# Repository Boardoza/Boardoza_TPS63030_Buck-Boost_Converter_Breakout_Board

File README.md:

# Boardoza TPS63030 Buck-Boost Converter Breakout Board
The TPS63030 High-Efficiency Buck-Boost Converter Breakout Board is a versatile power solution designed for battery-operated devices. It leverages the TPS63030 IC to efficiently convert input voltages from a wide range of battery chemistries, including two-cell or three-cell alkaline, NiCd, NiMH, or single-cell Li-ion/Li-polymer batteries. This board ensures a stable and adjustable power supply, supporting output currents up to 600 mA, even when the battery discharges to as low as 2.5V. With its high efficiency, compact design, and low quiescent current, the TPS63030 breakout board is ideal for portable electronics, wearable devices, and other applications requiring consistent performance regardless of battery charge state.

### [Click here to purchase!](https://www.ozdisan.com/maker-and-iot-products/boardoza/boardoza-modules/BOARDOZA-TPS63030/1206513)

|Front Side|Back Side|
|:---:|:---:|
| | |

---
## Key Features
- High Efficiency: Provides efficient power conversion, achieving up to 96% efficiency for extended battery life.
- Buck-Boost Capability: Supports both step-up and step-down voltage conversion for versatile power management.
- Adjustable Output Voltage: Allows for precise voltage control to match various device requirements.
- Automatic Mode Transition: Seamlessly transitions between step-down and boost modes based on input voltage.
- Safety Features: Includes overtemperature protection and load disconnect during shutdown for enhanced device safety.
- Compact Design: Small form factor for easy integration into portable applications and battery-operated devices.
- Low Quiescent Current: Consumes less than 50 μA in standby mode, optimizing power efficiency.

---

## Technical Specifications
**Input Voltage:**	1.8V ~ 5.5V

**Power Input Type:** Molex 2 pin 2.50 header

**Output Voltage:** 3.3V	

**Output Current:** 
- Up to 800 mA in Step-Down Mode (VIN = 3.6V to 5.5V)  
- Up to 500 mA in Boost Mode (VIN > 2.4V)  
 
**Functions:**	Buck-Boost Converter

**Efficiency:** Up to 96%

**Quiescent Current:** Less than 50 μA  

**Operating Temperature:**	-40°C ~ +85°C

**Board Dimensions:**	40mm x 60mm

---

## Board Pinout
| ( J1 ) Pin Number | Pin Name | Description |
|:---:|:---:|---|
| 1 | GND | Ground |
| 2 | VIN | Voltage Input Pin (1.8V ~ 5.5V) |

| ( J2 ) Pin Number | Pin Name | Description |
|:---:|:---:|---|
| 1 | GND | Ground |
| 2 | VIN SENSE | Can be used to measure the input voltage directly on the input capacitor. |

| ( J3 ) Pin Number | Pin Name | Description |
|:---:|:---:|---|
| 1 | HIGH | Power Supply |
| 2 | EN | Shorting jumper between the center pin EN and HIGH turns on the unit. Shorting jumper between the center pin EN and LOW turns the unit off. (Default: Pulled up to VIN in circuit) |
| 3 | LOW | Ground |

| ( J4 ) Pin Number | Pin Name | Description |
|:---:|:---:|---|
| 1 | GND | Ground |
| 2 | VOUT SENSE | Can be used to measure the output voltage directly on the output capacitor. |

| ( J5 ) Pin Number | Pin Name | Description |
|:---:|:---:|---|
| 1 | HIGH | Power Supply |
| 2 | PS/SYNC | The center pin of this jumpers is connected to the SYNC pin of the TPS63030 and is used to synchronize the unit with an external clock.This jumper also enables/disables the power-saving mode at light loads. To enable power-save, PS/SYNC must  shorting  to LOW. (Default: Pulled up to VIN in circuit) |
| 3 | LOW | Ground |

| ( J6 ) Pin Number | Pin Name | Description |
|:---:|:---:|---|
| 1 | GND | Ground |
| 2 | VOUT | Buck-boost converter output (3.3V) |

---
## Board Dimensions

---
## Step Files

[Boardoza TPS63030.step](./assets/TPS63030%20Step.step)

---
## Datasheet

[Boardoza TPS63030 Datasheet.pdf](./assets/TPS63030%20Datasheet.pdf)

---
## Version History
- V1.0.0 - Initial Release

---
## Support
- If you have any questions or need support, please contact support@boardoza.com

---
## License

Shield: [![CC BY-SA 4.0][cc-by-sa-shield]][cc-by-sa]

This work is licensed under a [Creative Commons Attribution-ShareAlike 4.0 International License][cc-by-sa].

[![CC BY-SA 4.0][cc-by-sa-image]][cc-by-sa]

[cc-by-sa]: http://creativecommons.org/licenses/by-sa/4.0/
[cc-by-sa-image]: https://licensebuttons.net/l/by-sa/4.0/88x31.png
[cc-by-sa-shield]: https://img.shields.io/badge/License-CC%20BY--SA%204.0-lightgrey.svg

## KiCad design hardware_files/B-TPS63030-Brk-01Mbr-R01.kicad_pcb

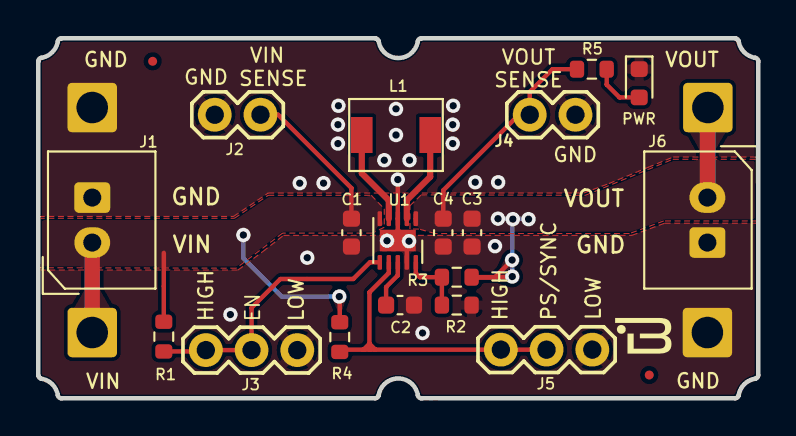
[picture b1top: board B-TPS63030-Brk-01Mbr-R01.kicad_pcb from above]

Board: 2 copper layers, 40.0 x 20.0 mm, 22 parts (0 on the bottom side), 10 nets.

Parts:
C1, C3, C4: 10uF; C_0603_1608Metric
C2: 100nF; C_0603_1608Metric
H1: VIN; SolderWire-1sqmm_1x01_D1.4mm_OD2.7mm
H2, H3: GND; SolderWire-1sqmm_1x01_D1.4mm_OD2.7mm
H4: VOUT; SolderWire-1sqmm_1x01_D1.4mm_OD2.7mm
J1, J6: 2317-02; 2317-02S_1x02_P2.50mm_Vertical
J2, J4: CONN_02; 1X02
J3: EN; 1X03
J5: PS/SYNC; 1X03
L1: SMPI04020-1R5M; SMPI04020
PWR: LED POWER; LED_0603_1608Metric
R1, R3, R4: 1M; R_0603_1608Metric
R2: 180K; R_0603_1608Metric
R5: 10K; R_0603_1608Metric
U1: TPS63030DSK; WSON-10-1EP_2.5x2.5mm_P0.5mm_EP1.2x2mm

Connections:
EN: J3.2, J3.3, R1.2, U1.6 (EN)
FB: R2.2, R3.1, U1.10 (FB)
GND: C1.2, C2.2, C3.2, C4.2, H2.1, H3.1, J1.2, J2.1, J3.1, J4.2, J5.1, J6.2, PWR.1 (K), R2.1, U1.3 (PGND), U1.9 (GND), U1.11 (PGND)
unnamed: PWR.2 (A), R5.2
unnamed: L1.2, U1.4 (L1)
unnamed: L1.1, U1.2 (L2)
unnamed: C2.1, U1.8 (VINA)
unnamed: C3.1, C4.1, H4.1, J4.1, J6.1, R3.2, R5.1, U1.1 (VOUT)
PS/SYNC: J5.2, J5.3, R4.2, U1.7 (PS/SYNC)
V_IN: C1.1, H1.1, J1.1, J2.2, R1.1, R4.1, U1.5 (VIN)

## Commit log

2024-12-26 Initial release for TPS63030 Breakout Board
